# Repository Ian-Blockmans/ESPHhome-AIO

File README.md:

# ESPHhome-AIO
 An all in one ESPHome development board (very WIP)

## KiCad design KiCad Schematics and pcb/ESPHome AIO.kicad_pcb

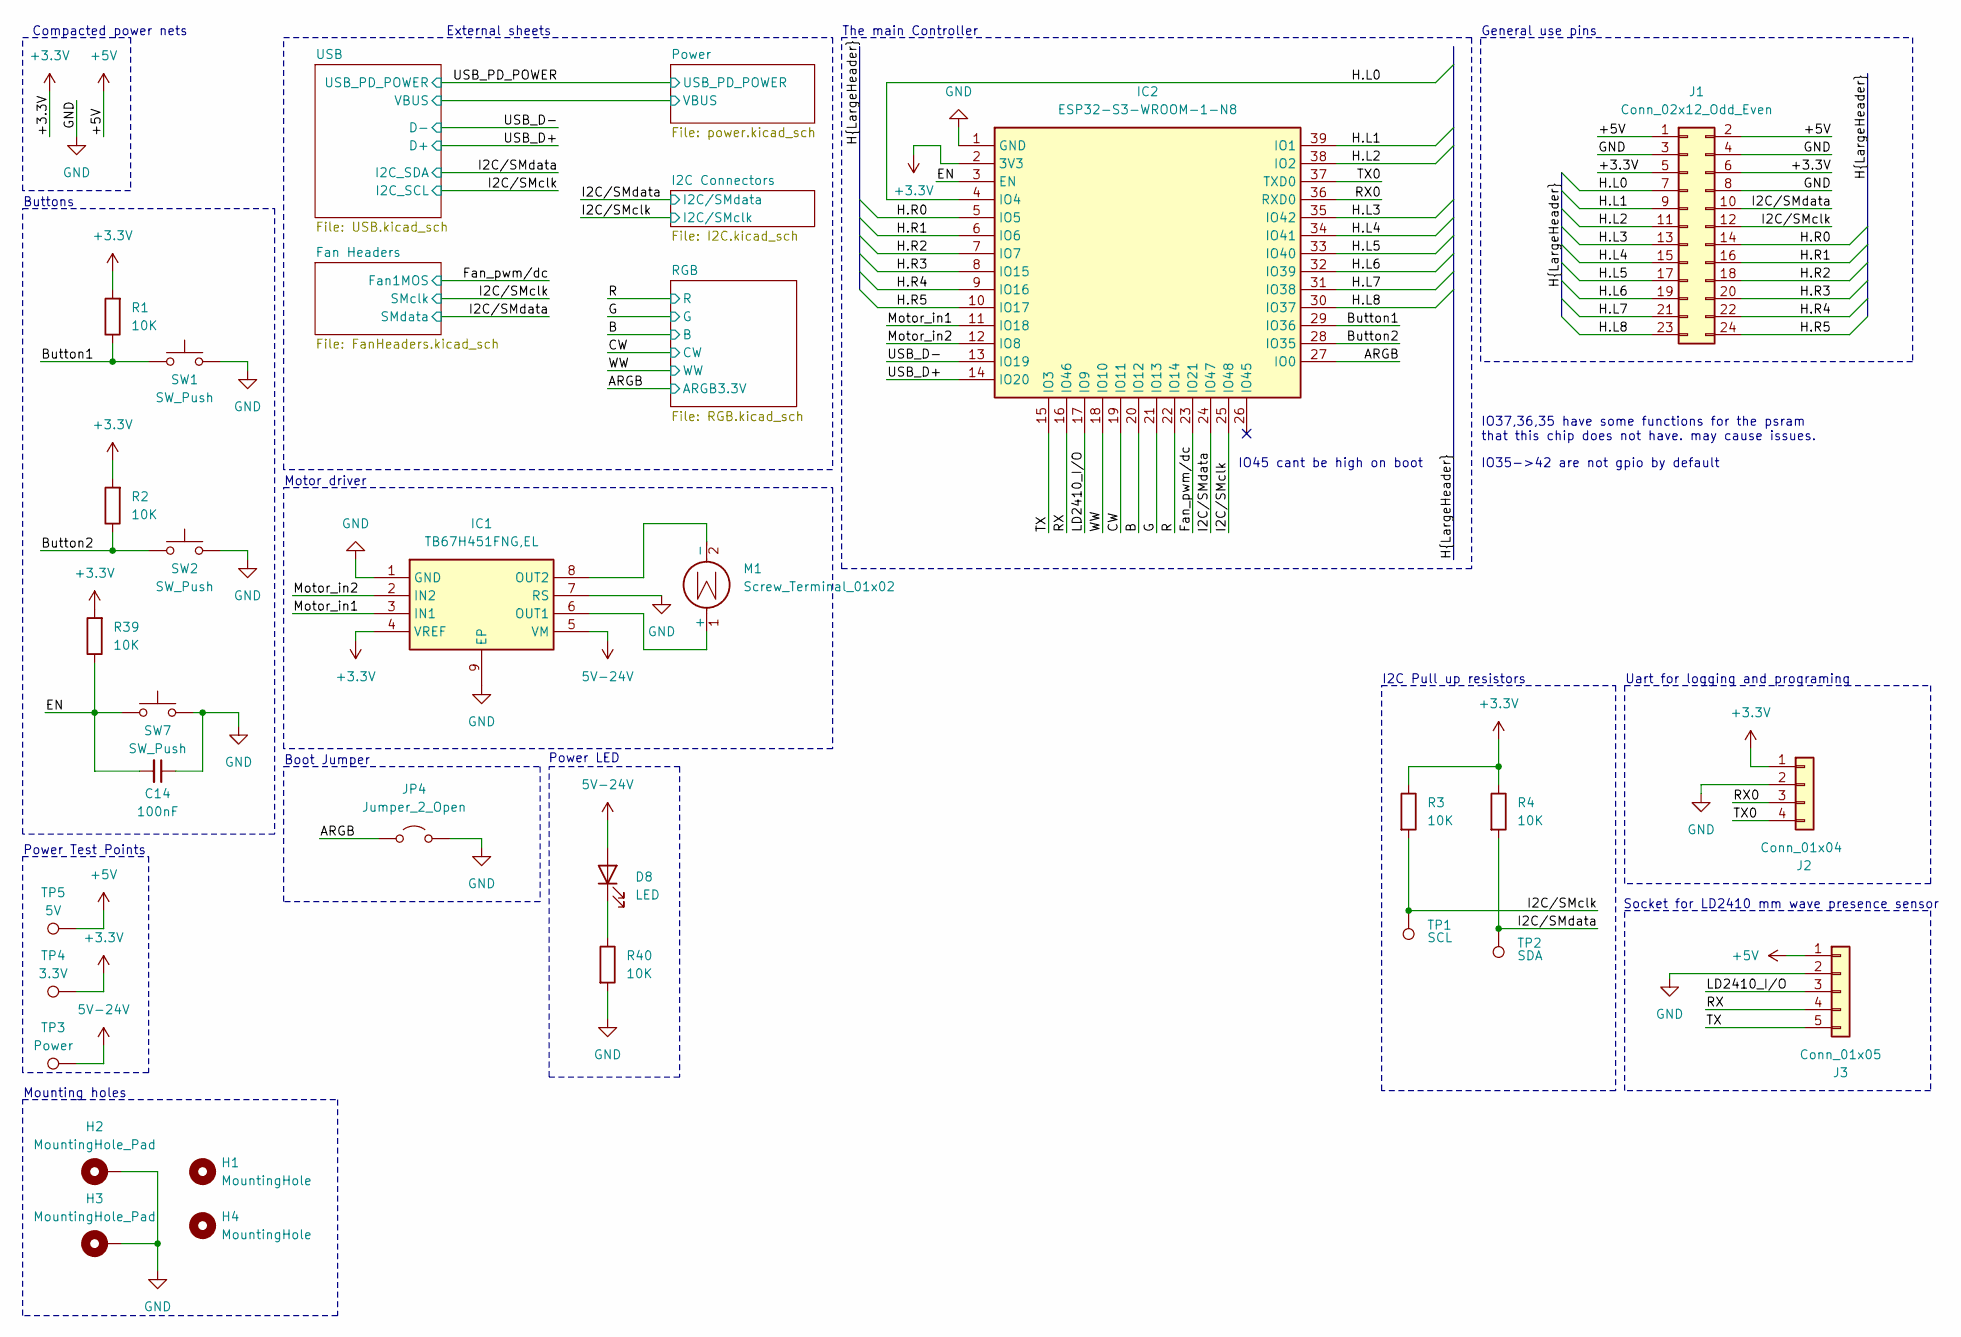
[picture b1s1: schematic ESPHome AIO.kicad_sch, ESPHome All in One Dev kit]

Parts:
C14: 100nF; C_0805_2012Metric
D8: LED; LED_0805_2012Metric
H1, H4: MountingHole; MountingHole_4.3mm_M4
H2, H3: MountingHole_Pad; MountingHole_4.3mm_M4_Pad
IC1: TB67H451FNG,EL; SOIC127P600X170-9N; Manufacturer_Part_Number TB67H451FNG,EL; Mouser Part Number 757-TB67H451FNGEL
IC2: ESP32-S3-WROOM-1-N8; ESP32S3WROOM1N8R8; Manufacturer_Part_Number ESP32-S3-WROOM-1-N8R8; Mouser Part Number 356-EP32S3WROOM1N8R8
J1: Conn_02x12_Odd_Even; PinHeader_2x12_P2.54mm_Vertical; LCSC C5383110
J2: Conn_01x04; PinHeader_1x04_P2.54mm_Vertical; LCSC C6332197
J3: Conn_01x05; PinHeader_1x05_P2.54mm_Vertical; LCSC C2935899
JP4: Jumper_2_Open; PinHeader_1x02_P2.54mm_Vertical
M1: Screw_Terminal_01x02; PhoenixContact_MSTBA_2,5_2-G-5,08_1x02_P5.08mm_Horizontal; LCSC C8383
R1, R2, R3, R4, R39, R40: 10K; R_0805_2012Metric; LCSC C17414
SW1, SW2, SW7: SW_Push; SW_PUSH_6mm_H7.3mm; LCSC C7463311
TP1: SCL; TestPoint_Loop_D2.60mm_Drill1.4mm_Beaded
TP2: SDA; TestPoint_Loop_D2.60mm_Drill1.4mm_Beaded
TP3: Power; TestPoint_Loop_D2.60mm_Drill1.4mm_Beaded
TP4: 3.3V; TestPoint_Loop_D2.60mm_Drill1.4mm_Beaded
TP5: 5V; TestPoint_Loop_D2.60mm_Drill1.4mm_Beaded

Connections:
5V-24V: D8.2 (A), IC1.5 (VM), TP3.1; also elsewhere on the board
+3.3V: IC1.4 (VREF), IC2.2 (3V3), J1.5, J1.6, J2.1, R1.2, R2.2, R3.1, R4.1, R39.2, TP4.1; also elsewhere on the board
+5V: J1.1, J1.2, J3.1, TP5.1; also elsewhere on the board
/ARGB: IC2.27 (IO0), JP4.1 (A); also elsewhere on the board
/B: IC2.20 (IO12); also elsewhere on the board
/Button1: IC2.29 (IO36), R1.1, SW1.1
/Button2: IC2.28 (IO35), R2.1, SW2.1
/CW: IC2.19 (IO11); also elsewhere on the board
/EN: C14.2, IC2.3 (EN), R39.1, SW7.1
/Fan_pwm/dc: IC2.23 (IO21); also elsewhere on the board
/G: IC2.21 (IO13); also elsewhere on the board
/H.L0: IC2.4 (IO4), J1.7
/H.L1: IC2.39 (IO1), J1.9
/H.L2: IC2.38 (IO2), J1.11
/H.L3: IC2.35 (IO42), J1.13
/H.L4: IC2.34 (IO41), J1.15
/H.L5: IC2.33 (IO40), J1.17
/H.L6: IC2.32 (IO39), J1.19
/H.L7: IC2.31 (IO38), J1.21
/H.L8: IC2.30 (IO37), J1.23
/H.R0: IC2.5 (IO5), J1.14
/H.R1: IC2.6 (IO6), J1.16
/H.R2: IC2.7 (IO7), J1.18
/H.R3: IC2.8 (IO15), J1.20
/H.R4: IC2.9 (IO16), J1.22
/H.R5: IC2.10 (IO17), J1.24
/I2C/SMclk: IC2.25 (IO48), J1.12, R3.2, TP1.1; also elsewhere on the board
/I2C/SMdata: IC2.24 (IO47), J1.10, R4.2, TP2.1; also elsewhere on the board
/LD2410_I/O: IC2.17 (IO9), J3.3
/Motor_in1: IC1.3 (IN1), IC2.11 (IO18)
/Motor_in2: IC1.2 (IN2), IC2.12 (IO8)
/R: IC2.22 (IO14); also elsewhere on the board
/RX: IC2.16 (IO46), J3.4
/RX0: IC2.36 (RXD0), J2.3
/TX: IC2.15 (IO3), J3.5
/TX0: IC2.37 (TXD0), J2.4
/USB_D+: IC2.14 (IO20); also elsewhere on the board
/USB_D-: IC2.13 (IO19); also elsewhere on the board
/WW: IC2.18 (IO10); also elsewhere on the board
unnamed: D8.1 (K), R40.1
unnamed: IC1.6 (OUT1), M1.1 (+)
unnamed: IC1.8 (OUT2), M1.2 (-)

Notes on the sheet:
Compacted power nets
Power LED
Boot Jumper
External sheets
Socket for LD2410 mm wave presence sensor
General use pins
IO45 cant be high on boot
The main Controller
Mounting holes
Power Test Points
Uart for logging and programing
I2C Pull up resistors
IO37,36,35 have some functions for the psram that this chip does not have. may cause issues.
Buttons
Motor driver
IO35->42 are not gpio by default

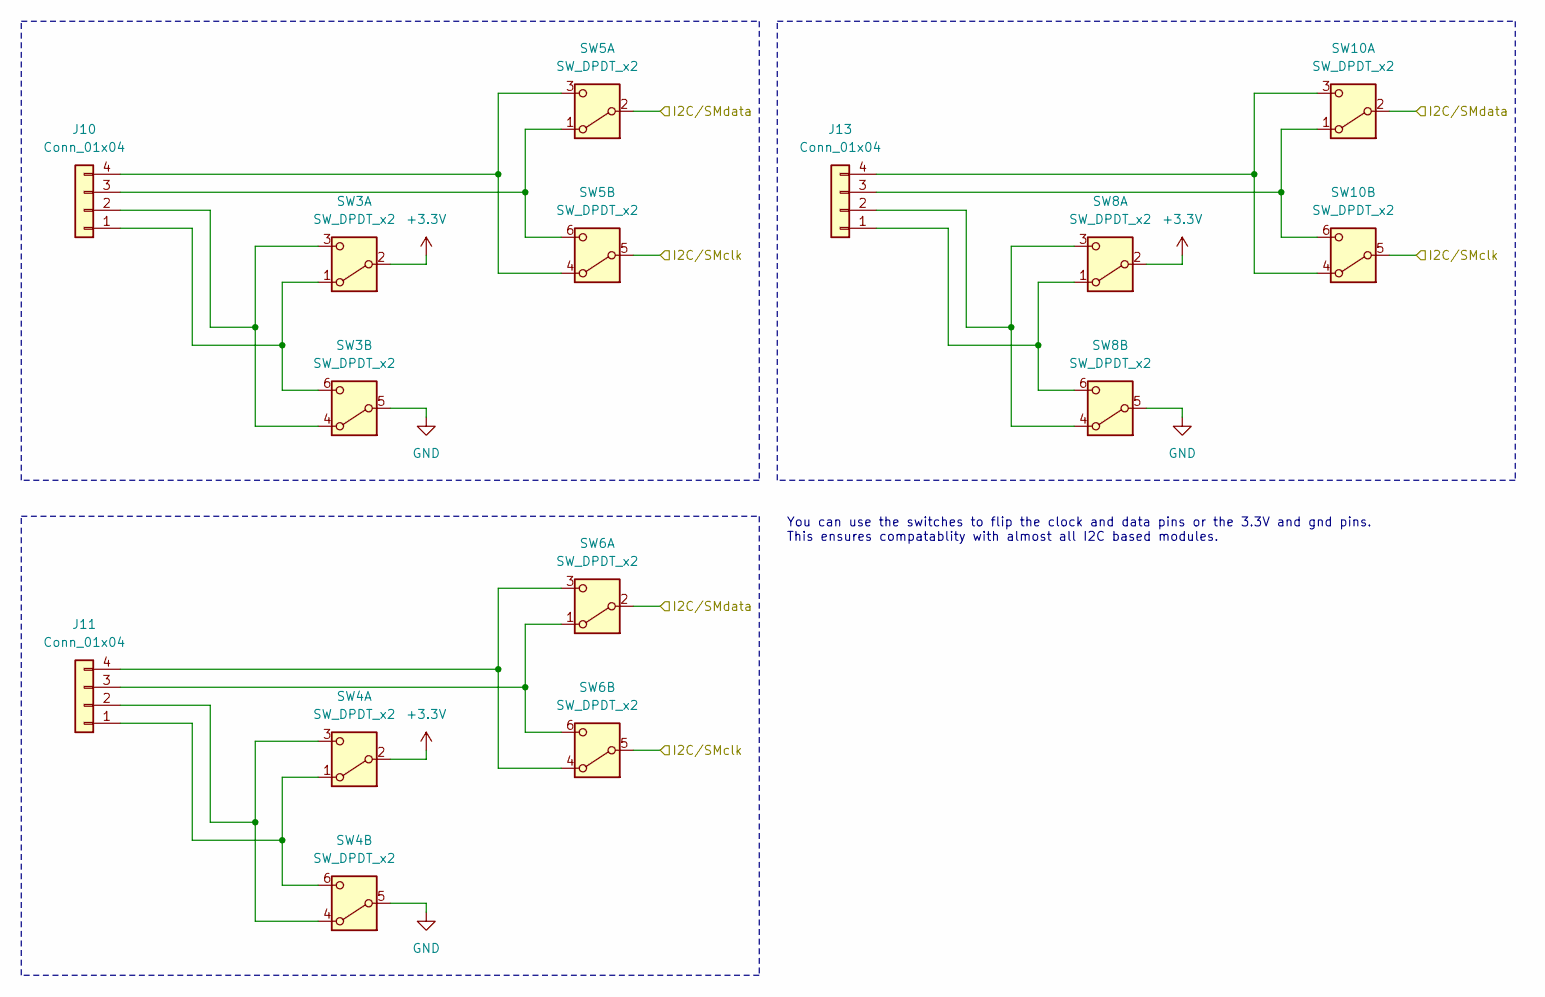
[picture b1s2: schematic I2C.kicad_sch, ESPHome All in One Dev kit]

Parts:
J10, J11, J13: Conn_01x04; PinHeader_1x04_P2.54mm_Vertical
SW3, SW4, SW5, SW6, SW8, SW10: SW_DPDT_x2; SW_CK_JS202011CQN_DPDT_Straight

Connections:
+3.3V: SW3.2 (B), SW4.2 (B), SW8.2 (B); also elsewhere on the board
/I2C/SMclk: SW5.5 (B), SW6.5 (B), SW10.5 (B); also elsewhere on the board
/I2C/SMdata: SW5.2 (B), SW6.2 (B), SW10.2 (B); also elsewhere on the board
unnamed: J10.1, SW3.1 (A), SW3.6 (C)
unnamed: J10.2, SW3.3 (C), SW3.4 (A)
unnamed: J10.3, SW5.1 (A), SW5.6 (C)
unnamed: J10.4, SW5.3 (C), SW5.4 (A)
unnamed: J11.1, SW4.1 (A), SW4.6 (C)
unnamed: J11.2, SW4.3 (C), SW4.4 (A)
unnamed: J11.3, SW6.1 (A), SW6.6 (C)
unnamed: J11.4, SW6.3 (C), SW6.4 (A)
unnamed: J13.1, SW8.1 (A), SW8.6 (C)
unnamed: J13.2, SW8.3 (C), SW8.4 (A)
unnamed: J13.3, SW10.1 (A), SW10.6 (C)
unnamed: J13.4, SW10.3 (C), SW10.4 (A)

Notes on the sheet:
You can use the switches to flip the clock and data pins or the 3.3V and gnd pins. This ensures compatablity with almost all I2C based modules.

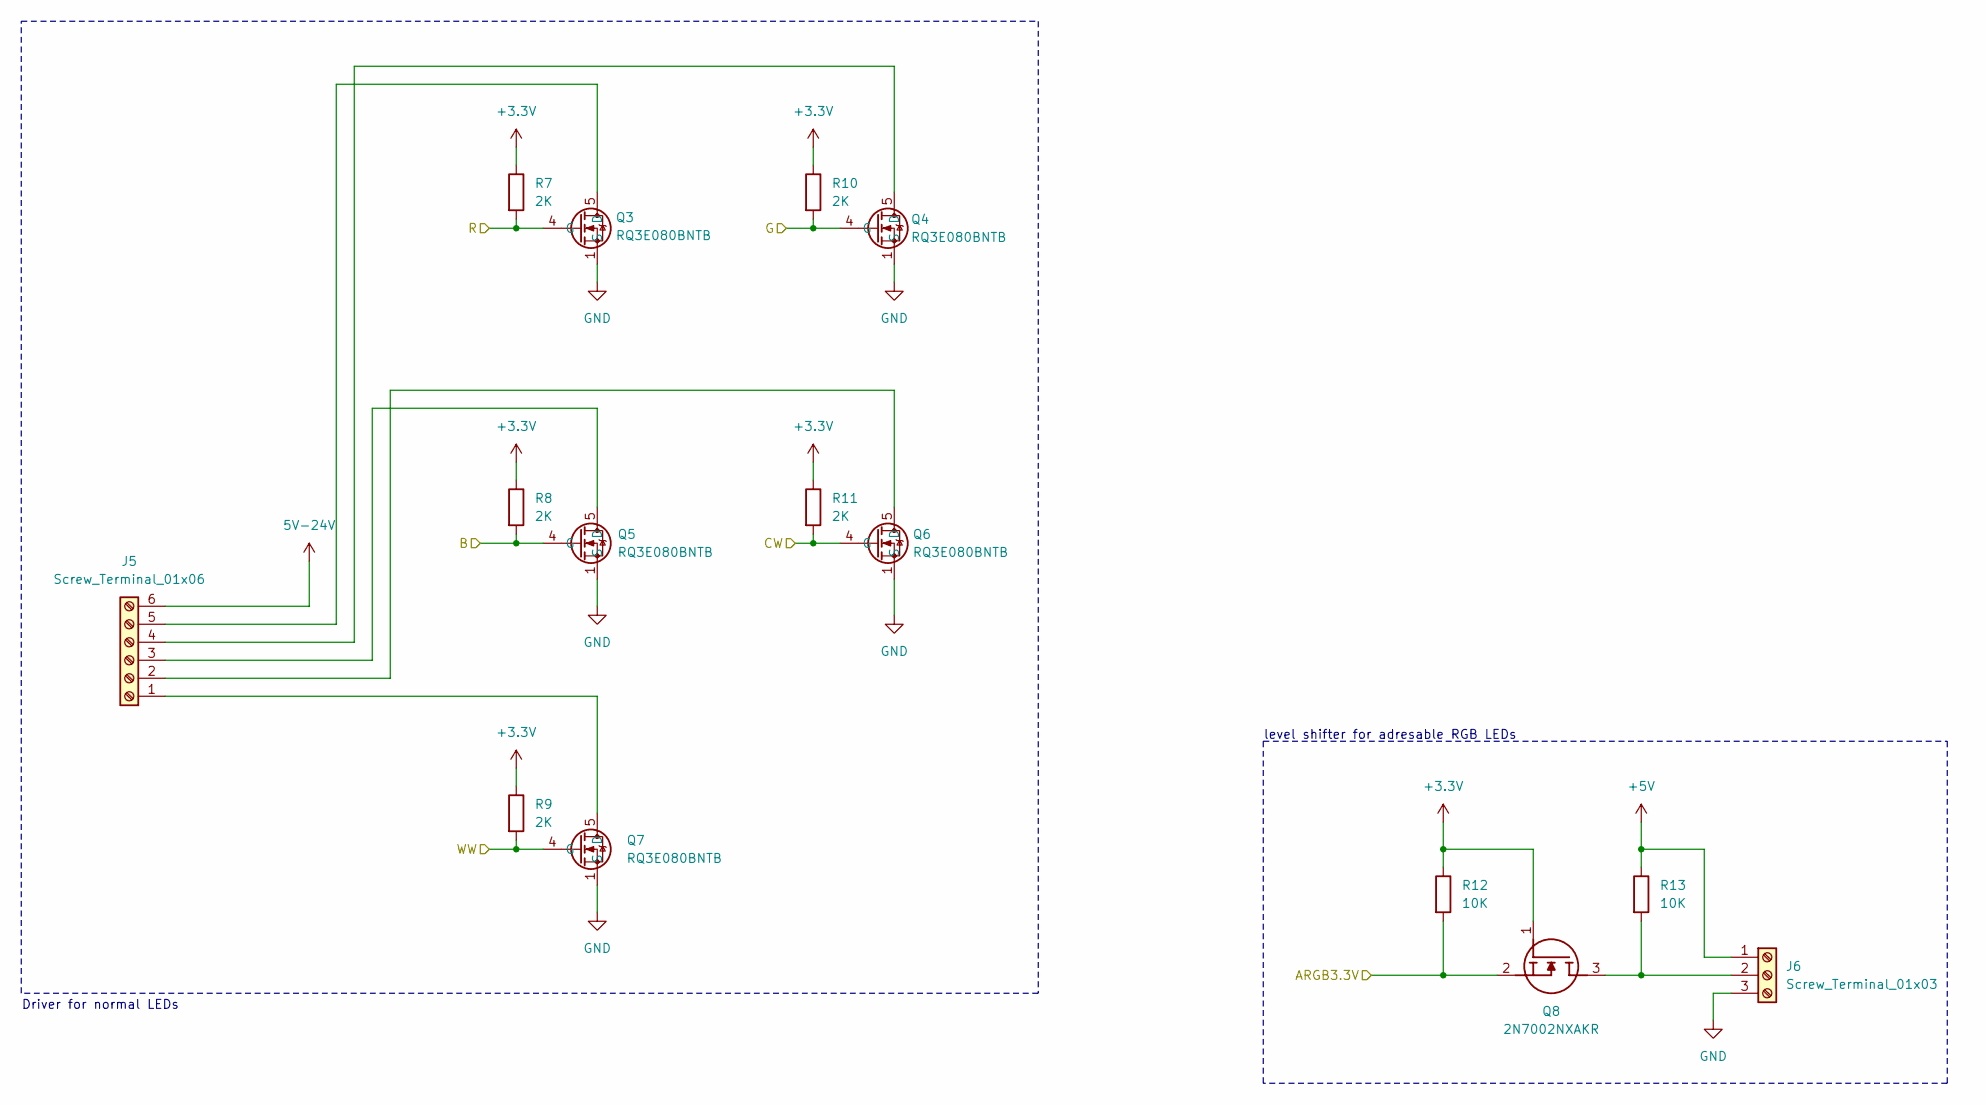
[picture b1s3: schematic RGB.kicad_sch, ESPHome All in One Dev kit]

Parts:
J5: Screw_Terminal_01x06; PhoenixContact_MSTBA_2,5_6-G-5,08_1x06_P5.08mm_Horizontal
J6: Screw_Terminal_01x03; PhoenixContact_MSTBA_2,5_3-G-5,08_1x03_P5.08mm_Horizontal
Q3, Q4, Q5, Q6, Q7: RQ3E080BNTB; Manufacturer_Part_Number RQ3E080BNTB; Mouser Part Number 755-RQ3E080BNTB
Q8: 2N7002NXAKR; SOT95P230X110-3N; Manufacturer_Part_Number 2N7002NXAKR; Mouser Part Number 771-2N7002NXAKR
R7, R8, R9, R10, R11: 2K; R_0805_2012Metric
R12, R13: 10K; R_0805_2012Metric

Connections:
5V-24V: J5.6; also elsewhere on the board
+3.3V: Q8.1 (G), R7.1, R8.1, R9.1, R10.1, R11.1, R12.1; also elsewhere on the board
+5V: J6.1, R13.1; also elsewhere on the board
/ARGB: Q8.2 (S), R12.2; also elsewhere on the board
/B: Q5.4 (G), R8.2; also elsewhere on the board
/CW: Q6.4 (G), R11.2; also elsewhere on the board
/G: Q4.4 (G), R10.2; also elsewhere on the board
/R: Q3.4 (G), R7.2; also elsewhere on the board
/WW: Q7.4 (G), R9.2; also elsewhere on the board
unnamed: J5.1, Q7.5 (D), Q7.6 (DRAIN_2), Q7.7 (DRAIN_3), Q7.8 (DRAIN_4), Q7.9 (DRAIN_5)
unnamed: J5.2, Q6.5 (D), Q6.6 (DRAIN_2), Q6.7 (DRAIN_3), Q6.8 (DRAIN_4), Q6.9 (DRAIN_5)
unnamed: J5.3, Q5.5 (D), Q5.6 (DRAIN_2), Q5.7 (DRAIN_3), Q5.8 (DRAIN_4), Q5.9 (DRAIN_5)
unnamed: J5.4, Q4.5 (D), Q4.6 (DRAIN_2), Q4.7 (DRAIN_3), Q4.8 (DRAIN_4), Q4.9 (DRAIN_5)
unnamed: J5.5, Q3.5 (D), Q3.6 (DRAIN_2), Q3.7 (DRAIN_3), Q3.8 (DRAIN_4), Q3.9 (DRAIN_5)
unnamed: J6.2, Q8.3 (D), R13.2

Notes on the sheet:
level shifter for adresable RGB LEDs
Driver for normal LEDs

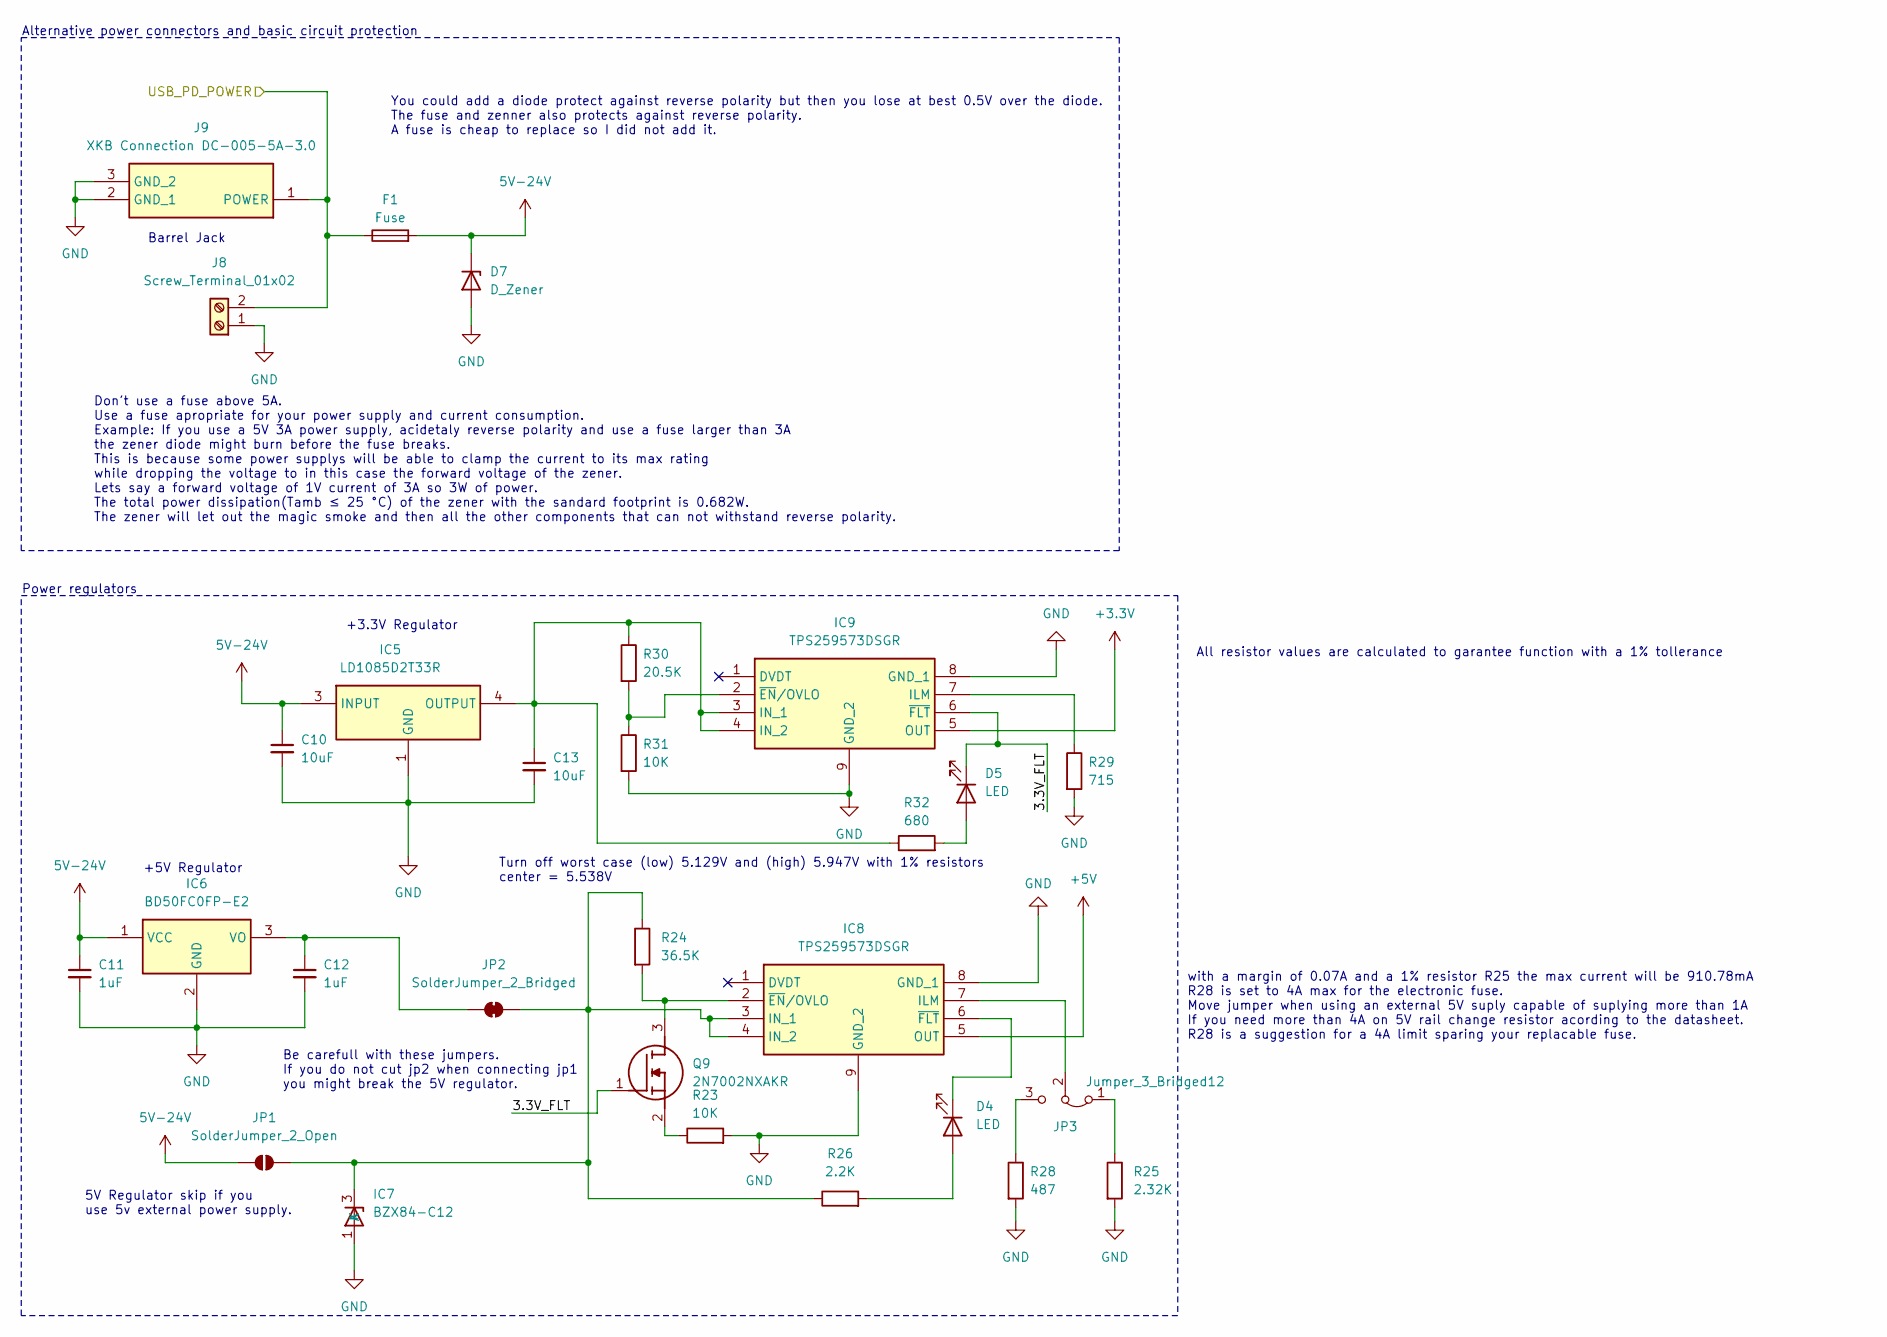
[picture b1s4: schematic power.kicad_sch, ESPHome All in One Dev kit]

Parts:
C10, C13: 10uF; C_0805_2012Metric
C11, C12: 1uF; C_0805_2012Metric
D4, D5: LED; LED_0805_2012Metric
D7: D_Zener; HPZRC28QX
F1: Fuse; Fuseholder_Littelfuse_Nano2_154x
IC5: LD1085D2T33R; Manufacturer_Part_Number LD1085D2T33R; Mouser Part Number 511-LD1085D2T33-TR
IC6: BD50FC0FP-E2; BD50FC0FPE2; Manufacturer_Part_Number BD50FC0FP-E2; Mouser Part Number 755-BD50FC0FP-E2
IC7: BZX84-C12; SOT95P230X110-3N; Manufacturer_Part_Number BZX84-C12; Mouser Part Number N/A
IC8, IC9: TPS259573DSGR; SON50P200X200X80-9N; Manufacturer_Part_Number TPS259573DSGR; Mouser Part Number 595-TPS259573DSGR
J8: Screw_Terminal_01x02; PhoenixContact_MSTBA_2,5_2-G-5,08_1x02_P5.08mm_Horizontal
J9: XKB Connection DC-005-5A-3.0; BarrelJack_Horizontal; Manufacturer_Part_Number 694106301002; Mouser Part Number 710-694106301002
JP1: SolderJumper_2_Open; SolderJumper-2_P1.3mm_Open_TrianglePad1.0x1.5mm
JP2: SolderJumper_2_Bridged; SolderJumper-2_P1.3mm_Open_TrianglePad1.0x1.5mm
JP3: Jumper_3_Bridged12; PinHeader_1x03_P2.54mm_Vertical
Q9: 2N7002NXAKR; SOT95P230X110-3N; Manufacturer_Part_Number 2N7002NXAKR; Mouser Part Number 771-2N7002NXAKR
R23, R31: 10K; R_0805_2012Metric
R24: 36.5K; R_0805_2012Metric
R25: 2.32K; R_0805_2012Metric
R26: 2.2K; R_0805_2012Metric
R28: 487; R_0805_2012Metric
R29: 715; R_0805_2012Metric
R30: 20.5K; R_0805_2012Metric
R32: 680; R_0805_2012Metric

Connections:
5V-24V: C10.1, C11.1, D7.1 (K), F1.2, IC5.3 (INPUT), IC6.1 (VCC), JP1.1 (A); also elsewhere on the board
+3.3V: IC9.5 (OUT); also elsewhere on the board
+5V: IC8.5 (OUT); also elsewhere on the board
/Power/3.3V_FLT: D5.1 (K), IC9.6 (~FLT), Q9.1 (G)
/USB_PD_POWER: F1.1, J8.2, J9.1 (POWER); also elsewhere on the board
unnamed: D4.1 (K), IC8.6 (~FLT)
unnamed: D5.2 (A), R32.2
unnamed: C13.1, IC5.4 (OUTPUT), IC9.3 (IN_1), IC9.4 (IN_2), R30.1, R32.1
unnamed: C12.1, IC6.3 (VO), JP2.1 (A)
unnamed: IC7.3 (K), IC8.3 (IN_1), IC8.4 (IN_2), JP1.2 (B), JP2.2 (B), R24.1, R26.1
unnamed: IC8.7 (ILM), JP3.2 (C)
unnamed: IC8.2 (~EN/OVLO), Q9.3 (D), R24.2
unnamed: IC9.7 (ILM), R29.1
unnamed: IC9.2 (~EN/OVLO), R30.2, R31.1
unnamed: JP3.1 (A), R25.1
unnamed: JP3.3 (B), R28.1
unnamed: Q9.2 (S), R23.1

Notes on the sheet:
Barrel Jack
You could add a diode protect against reverse polarity but then you lose at best 0.5V over the diode. The fuse and zenner also protects against reverse polarity. A fuse is cheap to replace so I did not add it.
Alternative power connectors and basic circuit protection
+3.3V Regulator
All resistor values are calculated to garantee function with a 1% tollerance
Power regulators
Be carefull with these jumpers. If you do not cut jp2 when connecting jp1 you might break the 5V regulator.
with a margin of 0.07A and a 1% resistor R25 the max current will be 910.78mA R28 is set to 4A max for the electronic fuse. Move jumper when using an external 5V suply capable of suplying more than 1A If you need more than 4A on 5V rail change resistor acording to the datasheet. R28 is a suggestion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
Turn off worst case (low) 5.129V and (high) 5.947V with 1% resistors center = 5.538V
5V Regulator skip if you use 5v external power supply.
+5V Regulator
Don't use a fuse above 5A. Use a fuse apropriate for your power supply and current consumption. Example: If you use a 5V 3A power supply, acidetaly reverse polarity and use a fuse larger than 3A the zener diode might burn before the fuse breaks. This is because some power supplys will be able to cl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

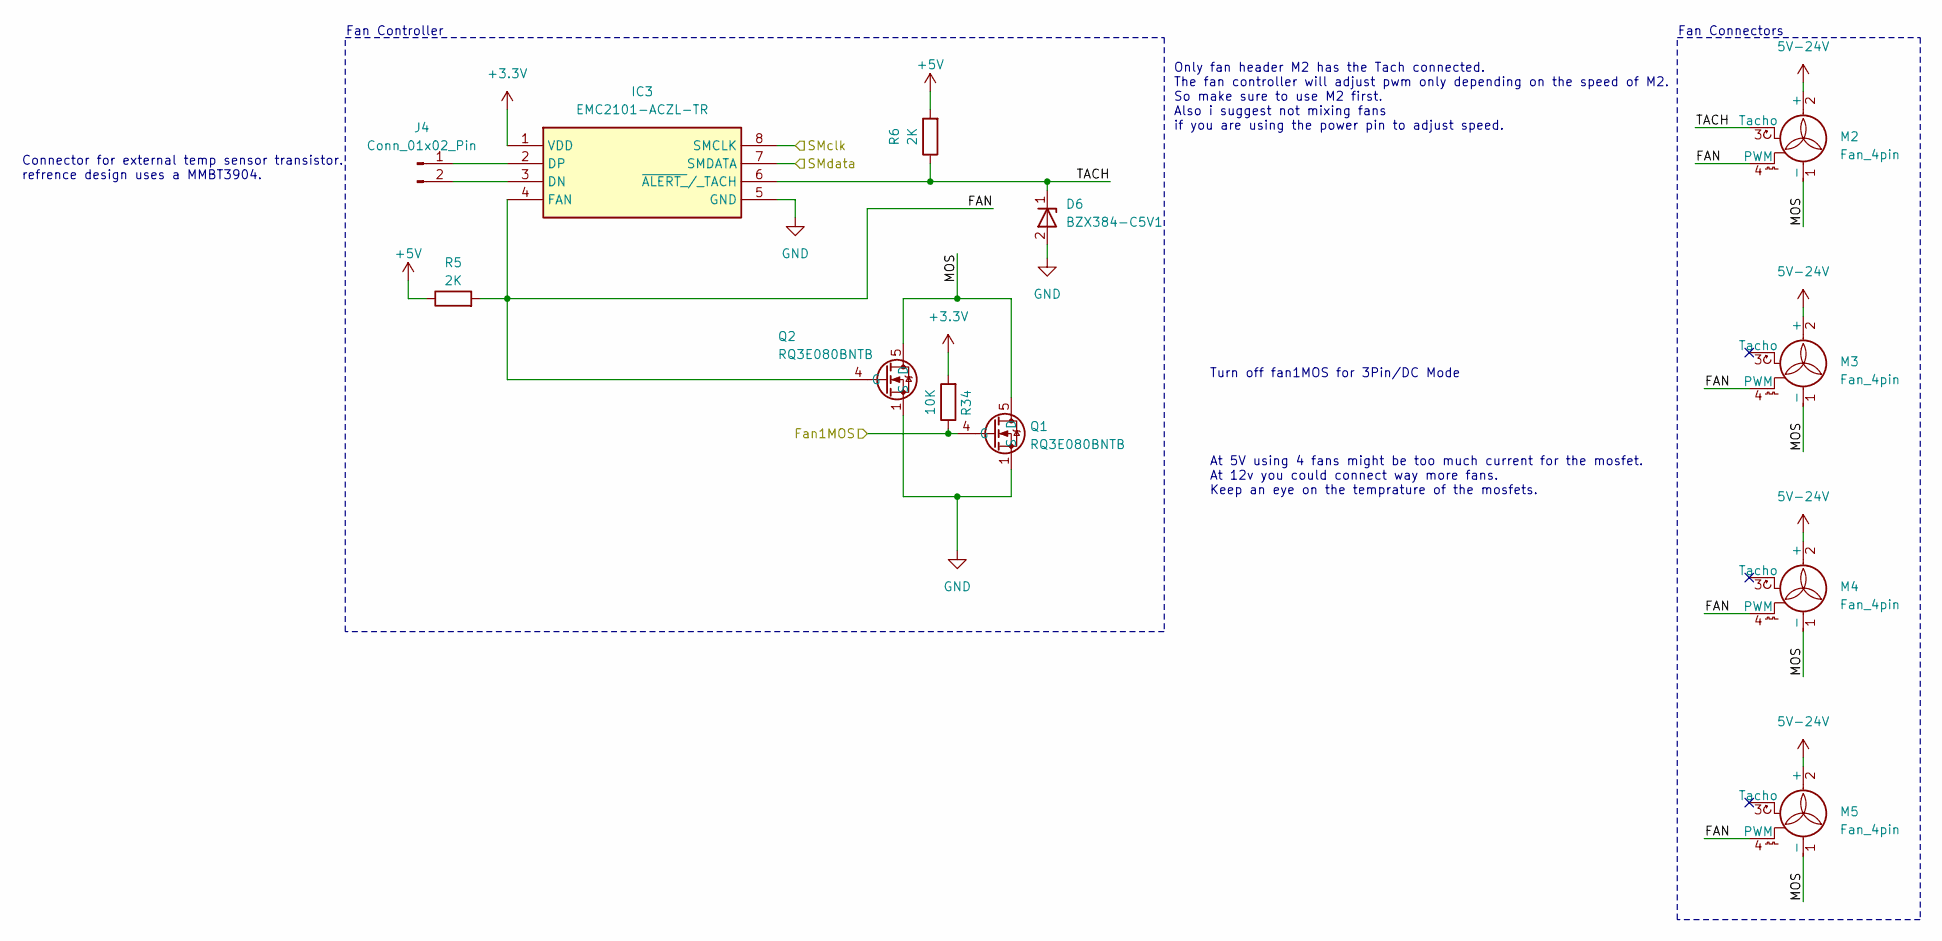
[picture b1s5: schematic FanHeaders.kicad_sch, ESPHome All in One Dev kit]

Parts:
D6: BZX384-C5V1; SOD2512X110N; Manufacturer_Part_Number BZX384-C5V1; Mouser Part Number N/A
IC3: EMC2101-ACZL-TR; SOP65P490X110-8N; Manufacturer_Part_Number EMC2101-ACZL-TR; Mouser Part Number 886-EMC2101-ACZL-TR
J4: Conn_01x02_Pin; JST_XH_B2B-XH-A_1x02_P2.50mm_Vertical
M2, M3, M4, M5: Fan_4pin; FanPinHeader_1x04_P2.54mm_Vertical
Q1, Q2: RQ3E080BNTB; Manufacturer_Part_Number RQ3E080BNTB; Mouser Part Number 755-RQ3E080BNTB
R5, R6: 2K; R_0805_2012Metric
R34: 10K; R_0805_2012Metric

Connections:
5V-24V: M2.2 (+), M3.2 (+), M4.2 (+), M5.2 (+); also elsewhere on the board
+3.3V: IC3.1 (VDD), R34.2; also elsewhere on the board
+5V: R5.1, R6.2; also elsewhere on the board
/Fan Headers/FAN: IC3.4 (FAN), M2.4 (PWM), M3.4 (PWM), M4.4 (PWM), M5.4 (PWM), Q2.4 (G), R5.2
/Fan Headers/MOS: M2.1 (-), M3.1 (-), M4.1 (-), M5.1 (-), Q1.5 (D), Q1.6 (DRAIN_2), Q1.7 (DRAIN_3), Q1.8 (DRAIN_4), Q1.9 (DRAIN_5), Q2.5 (D), Q2.6 (DRAIN_2), Q2.7 (DRAIN_3), Q2.8 (DRAIN_4), Q2.9 (DRAIN_5)
/Fan Headers/TACH: D6.1 (K), IC3.6 (~ALERT_/_TACH), M2.3 (Tacho), R6.1
/Fan_pwm/dc: Q1.4 (G), R34.1; also elsewhere on the board
/I2C/SMclk: IC3.8 (SMCLK); also elsewhere on the board
/I2C/SMdata: IC3.7 (SMDATA); also elsewhere on the board
unnamed: IC3.3 (DN), J4.2
unnamed: IC3.2 (DP), J4.1

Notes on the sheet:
Fan Controller
Connector for external temp sensor transistor. refrence design uses a MMBT3904.
Fan Connectors
At 5V using 4 fans might be too much current for the mosfet. At 12v you could connect way more fans. Keep an eye on the temprature of the mosfets.
Only fan header M2 has the Tach connected. The fan controller will adjust pwm only depending on the speed of M2. So make sure to use M2 first. Also i suggest not mixing fans if you are using the power pin to adjust speed.
Turn off fan1MOS for 3Pin/DC Mode

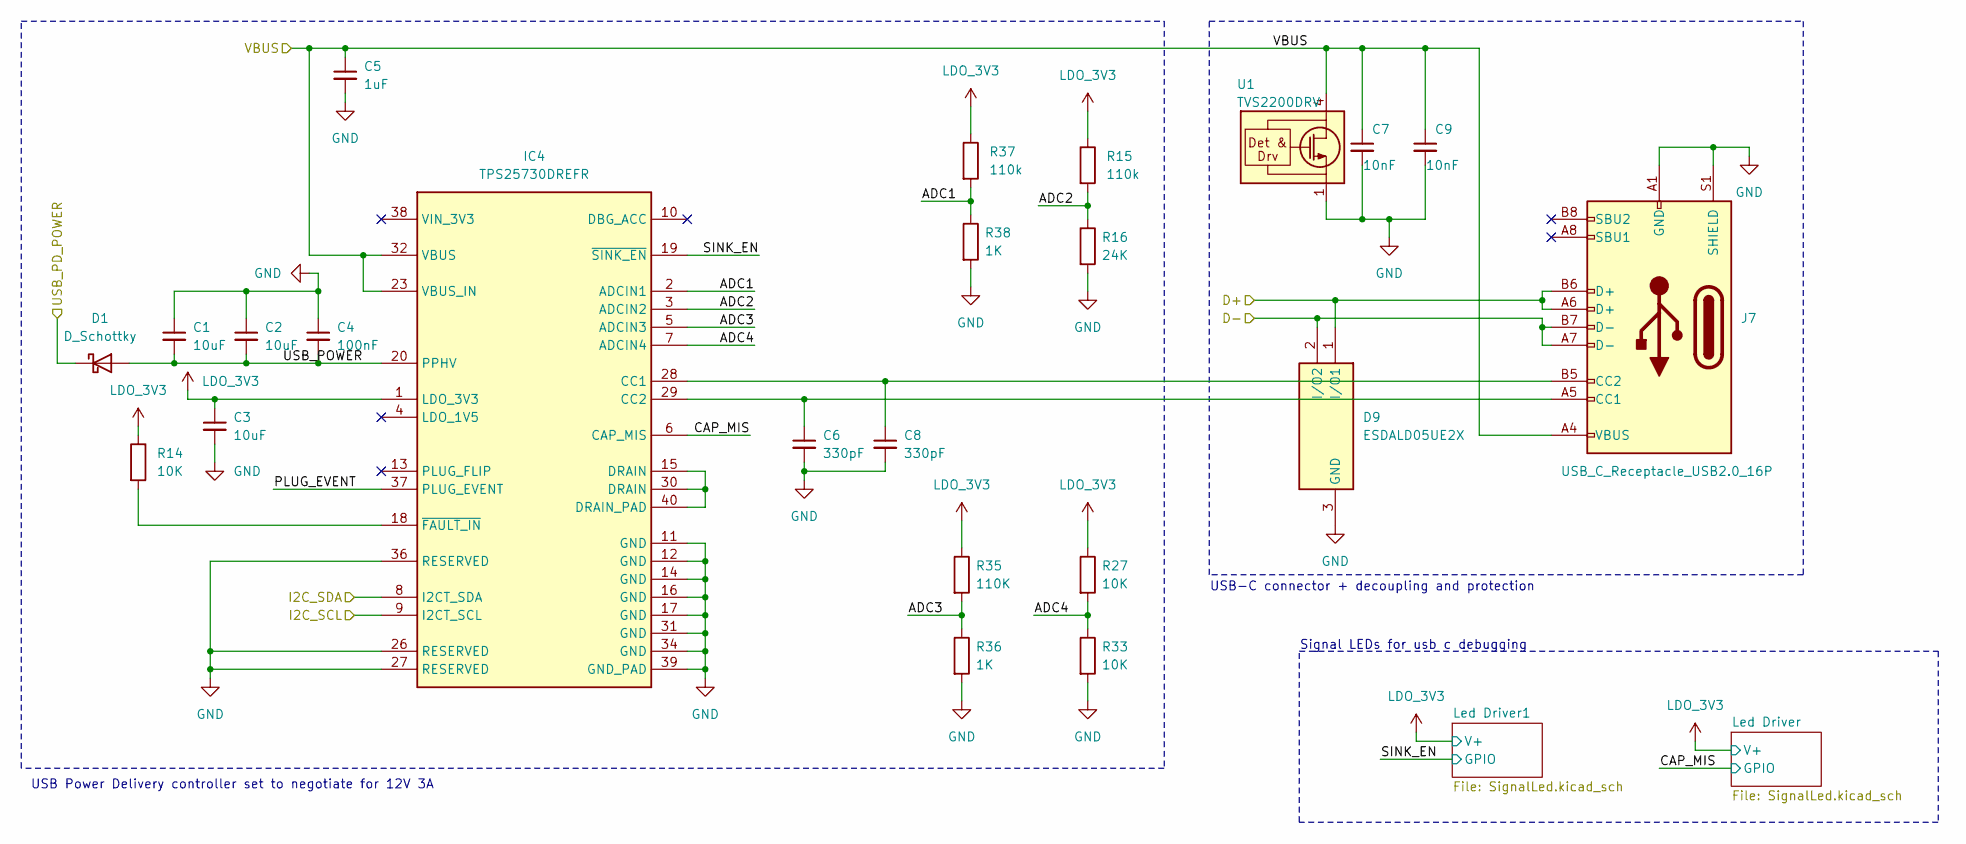
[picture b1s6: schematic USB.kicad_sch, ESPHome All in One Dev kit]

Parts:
C1, C2, C3: 10uF; C_0805_2012Metric
C4: 100nF; C_0805_2012Metric
C5: 1uF; C_0805_2012Metric
C6, C8: 330pF; C_0805_2012Metric
C7, C9: 10nF; C_0805_2012Metric
D1: D_Schottky; D_SMA
D9: ESDALD05UE2X; SOT95P240X115-3N; Manufacturer_Part_Number ESDALD05UE2X; Mouser Part Number 771-ESDALD05UE2X
IC4: TPS25730DREFR; Manufacturer_Part_Number TPS25730DREFR
J7: USB_C_Receptacle_USB2.0_16P; USB_C_Receptacle_G-Switch_GT-USB-7010ASV
R14, R27, R33: 10K; R_0805_2012Metric
R15, R37: 110k; R_0805_2012Metric
R16: 24K; R_0805_2012Metric
R35: 110K; R_0805_2012Metric
R36, R38: 1K; R_0805_2012Metric
U1: TVS2200DRV; WSON-6-1EP_2x2mm_P0.65mm_EP1x1.6mm

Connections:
/I2C/SMclk: IC4.9 (I2CT_SCL); also elsewhere on the board
/I2C/SMdata: IC4.8 (I2CT_SDA); also elsewhere on the board
/USB/ADC1: IC4.2 (ADCIN1), R37.2, R38.1
/USB/ADC2: IC4.3 (ADCIN2), R15.2, R16.1
/USB/ADC3: IC4.5 (ADCIN3), R35.2, R36.1
/USB/CAP_MIS: IC4.6 (CAP_MIS); also elsewhere on the board
/USB/PLUG_EVENT: IC4.37 (PLUG_EVENT)
/USB/SINK_EN: IC4.19 (~SINK_EN); also elsewhere on the board
/USB/USB_POWER: C1.2, C2.2, C4.2, D1.2 (A), IC4.20 (PPHV), IC4.21 (PPHV), IC4.22 (PPHV), IC4.41 (PPHV)
/USB/VBUS: C5.1, C7.1, C9.1, IC4.23 (VBUS_IN), IC4.24 (VBUS_IN), IC4.25 (VBUS_IN), IC4.32 (VBUS), IC4.33 (VBUS), IC4.42 (VBUS_IN), IC4.43 (VBUS), J7.A4 (VBUS), J7.A9 (VBUS), J7.B4 (VBUS), J7.B9 (VBUS), U1.4 (IN), U1.5 (IN), U1.6 (IN)
/USB_D+: D9.1 (I/O1), J7.A6 (D+), J7.B6 (D+); also elsewhere on the board
/USB_D-: D9.2 (I/O2), J7.A7 (D-), J7.B7 (D-); also elsewhere on the board
/USB_PD_POWER: D1.1 (K); also elsewhere on the board
unnamed: C8.1, IC4.28 (CC1), J7.B5 (CC2)
unnamed: C6.1, IC4.29 (CC2), J7.A5 (CC1)
unnamed: IC4.15 (DRAIN), IC4.30 (DRAIN), IC4.40 (DRAIN_PAD)
unnamed: IC4.18 (~FAULT_IN), R14.2

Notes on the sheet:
USB-C connector + decoupling and protection
Signal LEDs for usb c debugging
USB Power Delivery controller set to negotiate for 12V 3A

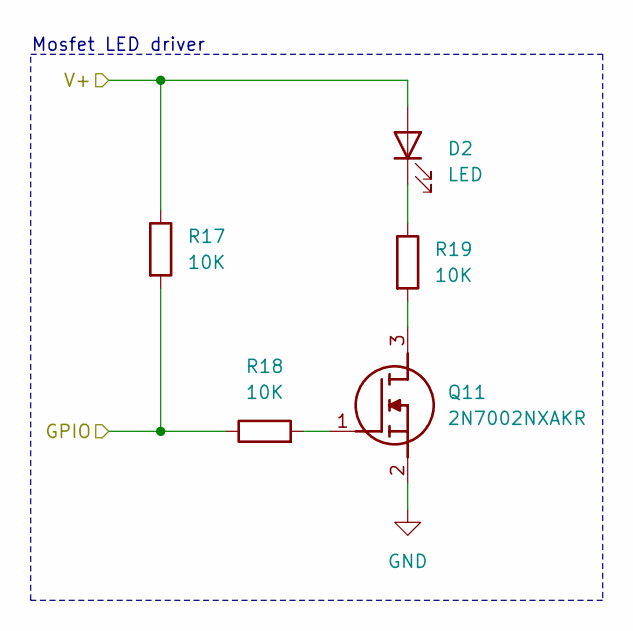
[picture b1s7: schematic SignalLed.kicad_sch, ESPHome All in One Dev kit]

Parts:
D2: LED; LED_0805_2012Metric
Q11: 2N7002NXAKR; SOT95P230X110-3N; Manufacturer_Part_Number 2N7002NXAKR; Mouser Part Number 771-2N7002NXAKR
R17, R18, R19: 10K; R_0805_2012Metric

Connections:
/USB/CAP_MIS: R17.2, R18.1; also elsewhere on the board
unnamed: D2.1 (K), R19.1
unnamed: Q11.3 (D), R19.2
unnamed: Q11.1 (G), R18.2

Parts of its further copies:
D3: LED; LED_0805_2012Metric
Q12: 2N7002NXAKR; SOT95P230X110-3N; Manufacturer_Part_Number 2N7002NXAKR; Mouser Part Number 771-2N7002NXAKR
R20, R21, R22: 10K; R_0805_2012Metric

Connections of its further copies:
/USB/SINK_EN: R20.2, R21.1; also elsewhere on the board
unnamed: D3.1 (K), R22.1
unnamed: Q12.3 (D), R22.2
unnamed: Q12.1 (G), R21.2

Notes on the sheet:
Mosfet LED driver

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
